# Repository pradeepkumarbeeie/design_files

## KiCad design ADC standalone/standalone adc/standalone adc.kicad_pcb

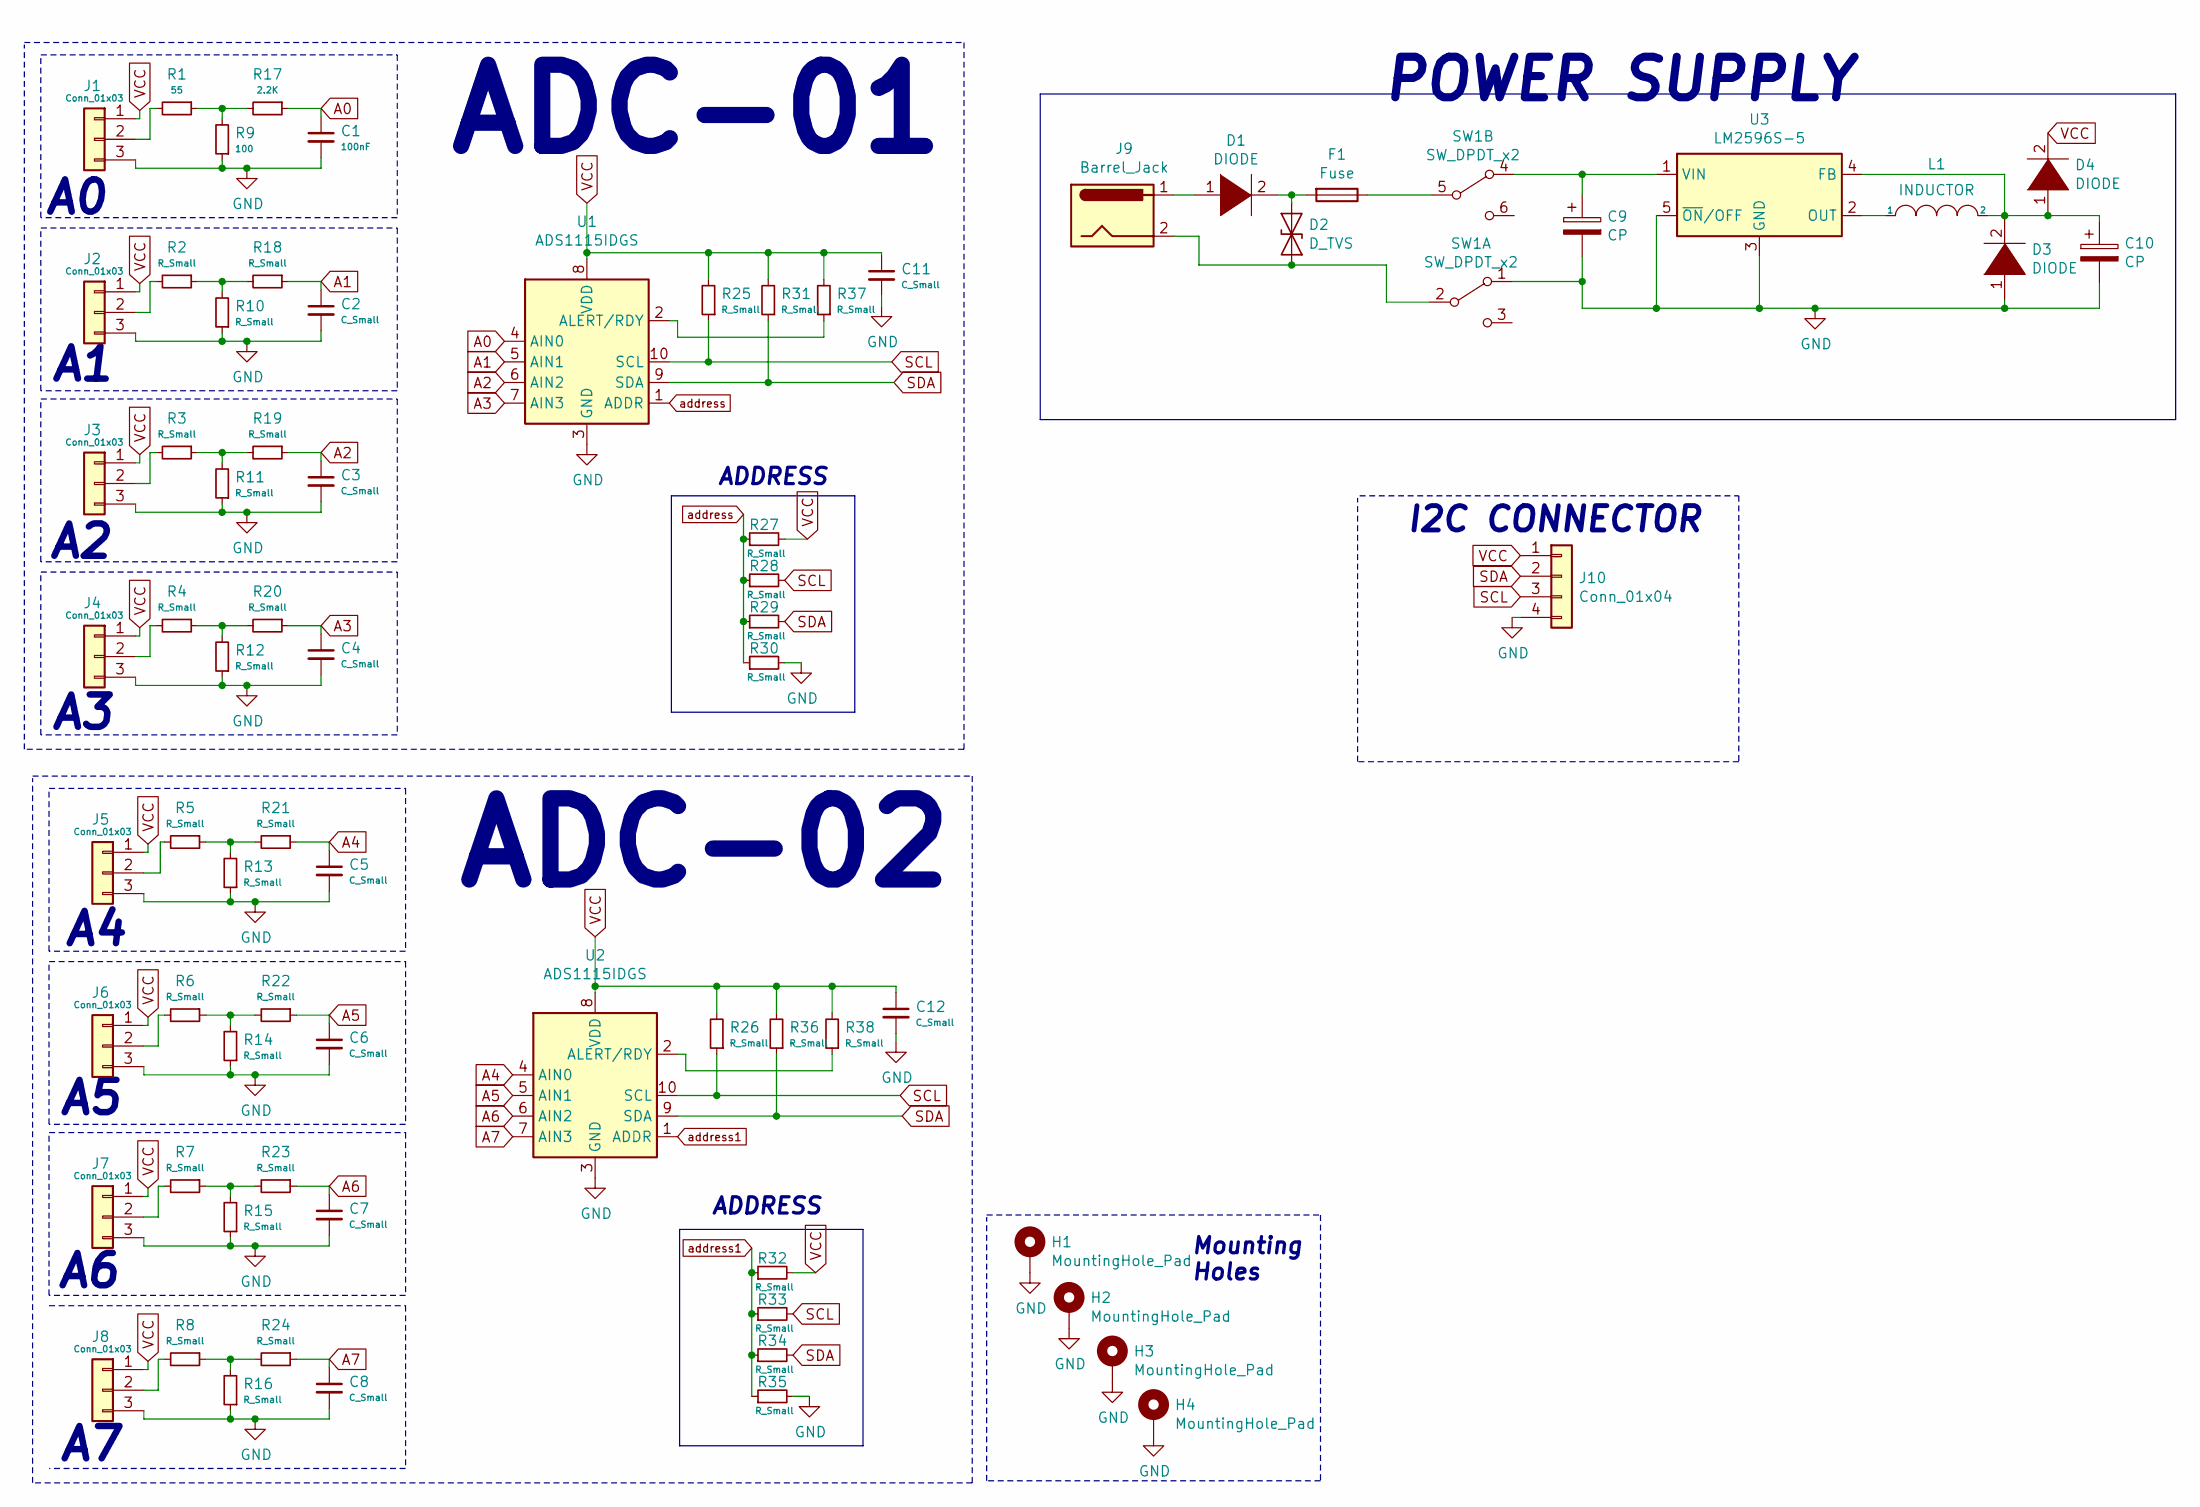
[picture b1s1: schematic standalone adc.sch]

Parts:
C1: 100nF; C_0805_2012Metric_Pad1.15x1.40mm_HandSolder
C2, C3, C4, C5, C6, C7, C8, C11, C12: C_Small; C_0805_2012Metric_Pad1.15x1.40mm_HandSolder
C9, C10: CP; C_Elec_10x10.2
D1, D3, D4: DIODE; D_SMA
D2: D_TVS; D_SMA
F1: Fuse; Fuseholder_Cylinder-5x20mm_Stelvio-Kontek_PTF78_Horizontal_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
H1, H2, H3, H4: MountingHole_Pad; MountingHole_3.2mm_M3_Pad_Via
J1, J2, J3, J4, J5, J6, J7, J8: Conn_01x03; JST_EH_B3B-EH-A_1x03_P2.50mm_Vertical
J9: Barrel_Jack; BarrelJack_Horizontal
J10: Conn_01x04; JST_EH_B4B-EH-A_1x04_P2.50mm_Vertical
L1: INDUCTOR; L_10.4x10.4_H4.8
R1: 55; R_0805_2012Metric_Pad1.15x1.40mm_HandSolder
R2, R3, R4, R5, R6, R7, R8, R10, R11, R12, R13, R14, R15, R16, R18, R19, R20, R21, R22, R23, R24, R25, R26, R27, R28, R29, R30, R31, R32, R33, R34, R35, R36, R37, R38: R_Small; R_0805_2012Metric_Pad1.15x1.40mm_HandSolder
R9: 100; R_0805_2012Metric_Pad1.15x1.40mm_HandSolder
R17: 2.2K; R_0805_2012Metric_Pad1.15x1.40mm_HandSolder
SW1: SW_DPDT_x2; SW_E-Switch_EG1271_DPDT
U1, U2: ADS1115IDGS; TSSOP-10_3x3mm_P0.5mm
U3: LM2596S-5; TO-263-5_TabPin3

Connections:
A0: C1.1, R17.1, U1.4 (AIN0)
A1: C2.1, R18.1, U1.5 (AIN1)
A2: C3.1, R19.1, U1.6 (AIN2)
A3: C4.1, R20.1, U1.7 (AIN3)
A4: C5.1, R21.1, U2.4 (AIN0)
A5: C6.1, R22.1, U2.5 (AIN1)
A6: C7.1, R23.1, U2.6 (AIN2)
A7: C8.1, R24.1, U2.7 (AIN3)
GND: C1.2, C2.2, C3.2, C4.2, C5.2, C6.2, C7.2, C8.2, C9.2, C10.2, C11.2, C12.2, D3.1 (K), H1.1, H2.1, H3.1, H4.1, J1.3, J2.3, J3.3, J4.3, J5.3, J6.3, J7.3, J8.3, J10.4, R9.1, R10.1, R11.1, R12.1, R13.1, R14.1, R15.1, R16.1, R30.2, R35.2, SW1.1 (A), U1.3 (GND), U2.3 (GND), U3.3 (GND), U3.5 (~ON~/OFF)
unnamed: C9.1, SW1.4 (A), U3.1 (VIN)
unnamed: C10.1, D3.2 (A), D4.1 (K), L1.2, U3.4 (FB)
unnamed: D1.1 (K), J9.1
unnamed: D1.2 (A), D2.1 (A1), F1.2
unnamed: D2.2 (A2), J9.2, SW1.2 (B)
unnamed: F1.1, SW1.5 (B)
unnamed: J1.2, R1.2
unnamed: J2.2, R2.2
unnamed: J3.2, R3.2
unnamed: J4.2, R4.2
unnamed: J5.2, R5.2
unnamed: J6.2, R6.2
unnamed: J7.2, R7.2
unnamed: J8.2, R8.2
unnamed: L1.1, U3.2 (OUT)
unnamed: R1.1, R9.2, R17.2
unnamed: R2.1, R10.2, R18.2
unnamed: R3.1, R11.2, R19.2
unnamed: R4.1, R12.2, R20.2
unnamed: R5.1, R13.2, R21.2
unnamed: R6.1, R14.2, R22.2
unnamed: R7.1, R15.2, R23.2
unnamed: R8.1, R16.2, R24.2
unnamed: R37.1, U1.2 (ALERT/RDY)
unnamed: R38.1, U2.2 (ALERT/RDY)
SCL: J10.3, R25.1, R26.1, R28.2, R33.2, U1.10 (SCL), U2.10 (SCL)
SDA: J10.2, R29.2, R31.1, R34.2, R36.1, U1.9 (SDA), U2.9 (SDA)
VCC: C11.1, C12.1, D4.2 (A), J1.1, J2.1, J3.1, J4.1, J5.1, J6.1, J7.1, J8.1, J10.1, R25.2, R26.2, R27.2, R31.2, R32.2, R36.2, R37.2, R38.2, U1.8 (VDD), U2.8 (VDD)
address: R27.1, R28.1, R29.1, R30.1, U1.1 (ADDR)
address1: R32.1, R33.1, R34.1, R35.1, U2.1 (ADDR)

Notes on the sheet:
ADC-01
ADC-02
POWER SUPPLY
I2C CONNECTOR
Mounting Holes
ADDRESS

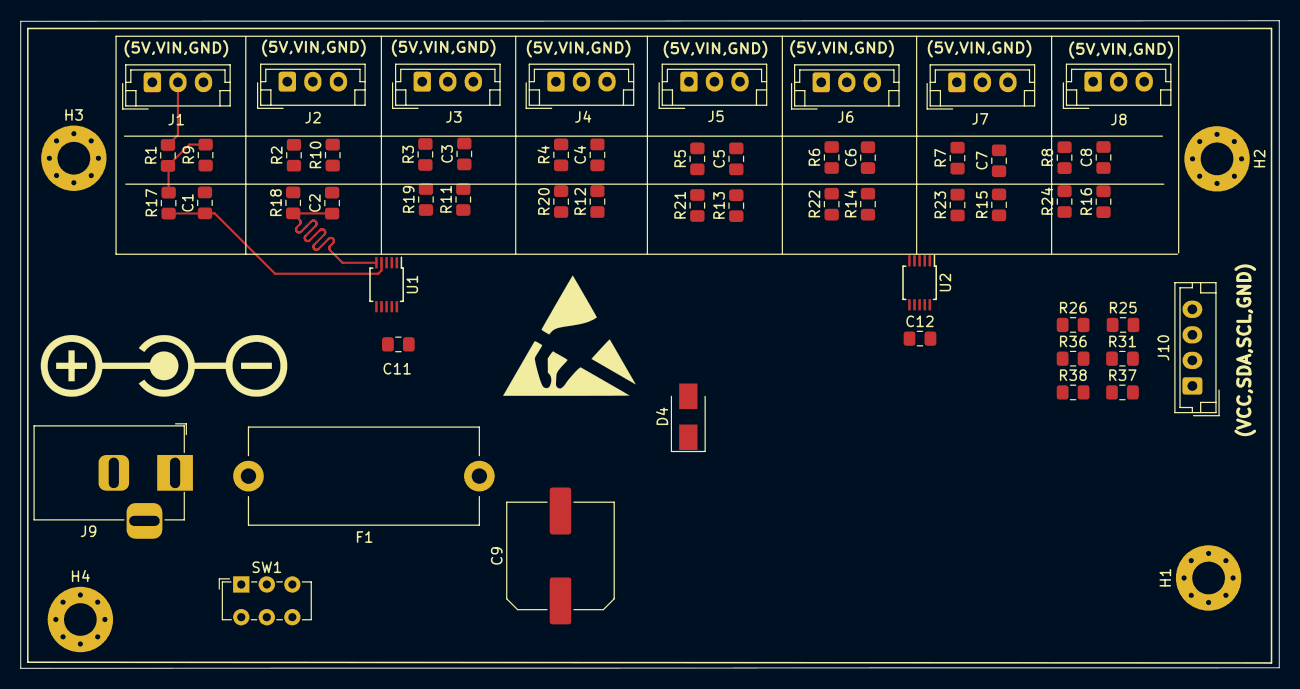
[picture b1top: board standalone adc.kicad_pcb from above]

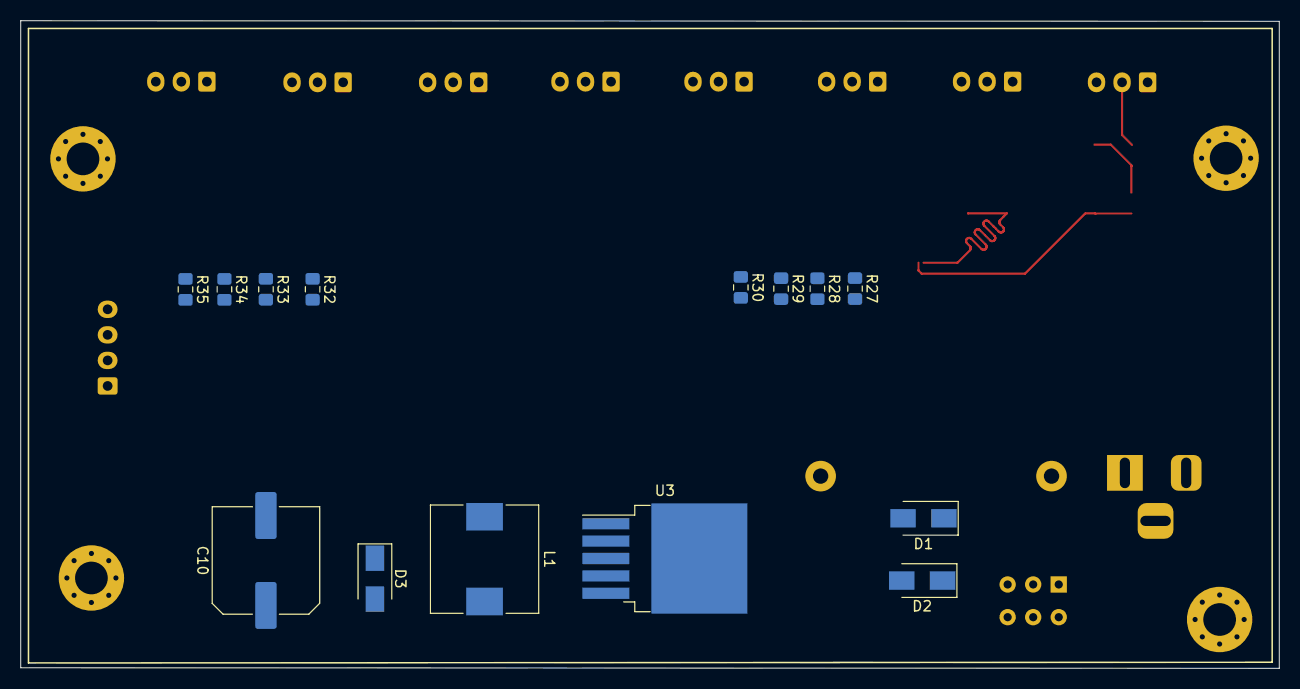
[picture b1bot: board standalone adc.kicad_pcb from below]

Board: 2 copper layers, 123.2 x 63.4 mm, 74 parts (14 on the bottom side), 39 nets.

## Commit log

2021-07-06 without layout
